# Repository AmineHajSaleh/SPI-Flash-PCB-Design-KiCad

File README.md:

# SPI Flash Memory PCB Design | KiCad

### 2-Layer PCB Design — W25Q32JV SPI Flash Memory

A personal electronics project focused on electronic schematic design, PCB layout, signal routing, power distribution, and design verification using **KiCad**.

The objective was to design a 2-layer SPI Flash memory breakout board for interfacing with an external STM32 microcontroller.

This project was developed to strengthen my practical skills in PCB design and routing.

---

## 1. PCB 3D Visualization

The 3D visualization shows the component placement, SPI connector, PCB dimensions, and silkscreen labeling.

---

## 2. Electronic Schematic

The electronic schematic was designed around the **W25Q32JVSS SPI Flash memory**.

### Main Components

| Reference | Component | Function |
|-----------|-----------|----------|
| U1 | W25Q32JVSS | 32 Mbit SPI Flash memory |
| R1 | 10 kΩ | CS pull-up resistor |
| C1 | 100 nF | Power supply decoupling |
| J1 | 6-pin connector | SPI interface with STM32 |

### Schematic Design

- 3.3 V power supply
- SPI communication: CS, SCK, MOSI, MISO
- 100 nF decoupling capacitor between VCC and GND
- 10 kΩ pull-up resistor on CS
- WP and HOLD pins connected to 3.3 V
- External STM32 connection through a 6-pin connector

The schematic was checked using KiCad's Electrical Rules Checker (ERC).

---

## 3. PCB Layout & Routing

The PCB was designed using a **2-layer architecture**.

### Layer Configuration

| Layer | Function |
|-------|----------|
| F.Cu | SPI signals and 3.3 V power routing |
| B.Cu | Ground copper plane and necessary signal routing |
| F.Silkscreen | Component references and connector labels |
| Edge.Cuts | Physical PCB outline |

### PCB Routing Decisions

- Placed the SPI Flash memory close to the connector.
- Positioned the decoupling capacitor near the VCC pin.
- Placed the CS pull-up resistor close to the memory.
- Routed SPI signals while respecting electrical clearances.
- Used vias where necessary to avoid trace crossings.
- Implemented a ground copper plane on B.Cu.
- Connected ground pads through vias.
- Optimized component placement to reduce unnecessary trace lengths.

---

## 4. SPI Interface

The PCB is designed to communicate with an external STM32 microcontroller using SPI.

### Connector Pinout

| J1 Pin | Signal | Description |
|--------|--------|-------------|
| 1 | 3V3 | 3.3 V power supply |
| 2 | CS | Chip Select |
| 3 | MISO | Master In Slave Out |
| 4 | SCK | SPI Clock |
| 5 | MOSI | Master Out Slave In |
| 6 | GND | Ground |

The external STM32 board must provide a regulated 3.3 V supply and compatible SPI logic levels.

---

## 5. PCB Design Considerations

### Component Placement

Component placement was organized to simplify routing and reduce connection lengths.

Special attention was given to the decoupling capacitor, which was placed close to the memory power supply pin.

### Power Distribution

The PCB uses a 3.3 V power supply.

The power routing was designed with consideration for trace width, connection lengths, and local decoupling.

### Ground Plane

A ground copper zone was implemented on the bottom copper layer.

Ground vias were used to connect component ground pads to the ground plane.

### Signal Routing

SPI signal traces were routed while avoiding electrical crossings on the same copper layer.

The placement and routing were progressively optimized to reduce unnecessary detours.

### EMC Considerations

Basic electromagnetic compatibility principles were considered during the design:

- Reducing unnecessary routing loops
- Keeping the decoupling connections short
- Considering signal return paths
- Preserving ground plane continuity where possible

Formal EMC testing has not been performed.

---

## 6. Design Verification

The following design steps were completed:

- [x] Electronic schematic design
- [x] Component selection
- [x] Footprint assignment
- [x] Electrical Rules Check (ERC)
- [x] PCB component placement
- [x] Signal and power routing
- [x] Ground plane implementation
- [x] Design Rules Check (DRC)
- [x] Silkscreen labeling
- [x] 3D PCB visualization
- [ ] Physical PCB manufacturing
- [ ] Hardware testing
- [ ] SPI communication validation with STM32

### Validation Status

The schematic and PCB were checked using KiCad ERC and DRC tools.

**The PCB has not yet been manufactured or physically tested.**

Therefore, electrical operation and SPI communication have not yet been experimentally validated.

---

## 7. Project Files

| File | Description |
|------|-------------|
| `SPI_FLASH_STM32.kicad_pro` | KiCad project configuration |
| `SPI_FLASH_STM32.kicad_sch` | Electronic schematic |
| `SPI_FLASH_STM32.kicad_pcb` | PCB layout and routing |
| `images/schematic.png` | Electronic schematic screenshot |
| `images/pcb-layout.png` | PCB routing screenshot |
| `images/pcb-3d.png` | 3D PCB visualization |

The KiCad source files are included to allow the schematic and PCB design to be inspected and modified.

---

## 8. Tools & Technical Skills

### Software

- KiCad Schematic Editor
- KiCad PCB Editor
- KiCad 3D Viewer
- KiCad ERC / DRC

### Skills Practiced

- Electronic schematic design
- Component footprint selection
- PCB component placement
- Two-layer PCB routing
- SPI interface design
- Power distribution
- Decoupling capacitor placement
- Ground plane implementation
- Via placement
- Design rule verification
- PCB documentation

---

## 9. Future Improvements

- Further optimization of PCB dimensions
- Additional review of signal routing and ground return paths
- Manufacturing file generation and verification
- PCB prototype manufacturing
- Component assembly and soldering
- Hardware testing using an STM32 microcontroller
- SPI JEDEC ID reading
- Flash memory read/write functional testing

---

## 10. Author

**Amine Haj Salah**

Electronics & Embedded Systems

[LinkedIn](https://www.linkedin.com/in/amine-haj-salah/) |
[GitHub](https://github.com/aminehajsaleh) |
[Portfolio](https://aminehajsaleh.github.io/PORTFOLIO/)

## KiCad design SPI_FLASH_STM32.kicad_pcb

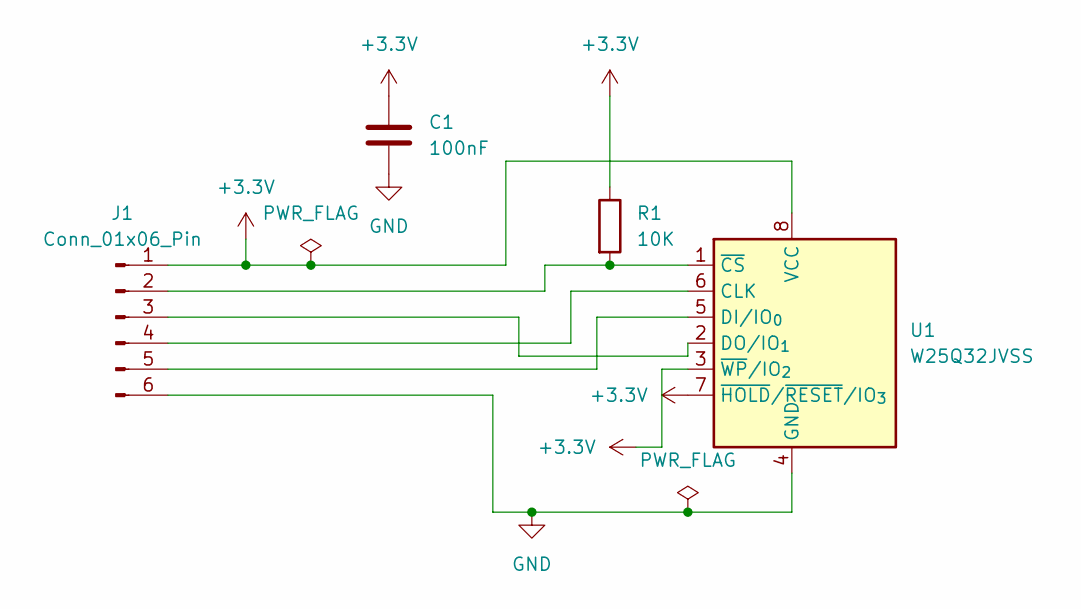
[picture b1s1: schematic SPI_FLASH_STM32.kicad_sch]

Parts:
C1: 100nF; C_0805_2012Metric
J1: Conn_01x06_Pin; PinHeader_1x06_P2.54mm_Vertical
R1: 10K; R_0805_2012Metric
U1: W25Q32JVSS; SOIC-8_5.3x5.3mm_P1.27mm

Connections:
+3.3V: C1.1, J1.1, R1.1, U1.3 (~WP/IO_{2}), U1.7 (~HOLD/~RESET/IO_{3}), U1.8 (VCC)
GND: C1.2, J1.6, U1.4 (GND)
unnamed: J1.2, R1.2, U1.1 (~CS)
unnamed: J1.3, U1.2 (DO/IO_{1})
unnamed: J1.4, U1.6 (CLK)
unnamed: J1.5, U1.5 (DI/IO_{0})

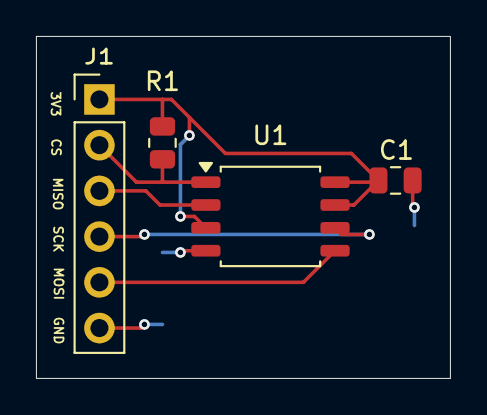
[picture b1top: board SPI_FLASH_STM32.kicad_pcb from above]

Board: 2 copper layers, 23.0 x 19.0 mm, 4 parts (0 on the bottom side), 6 nets.
